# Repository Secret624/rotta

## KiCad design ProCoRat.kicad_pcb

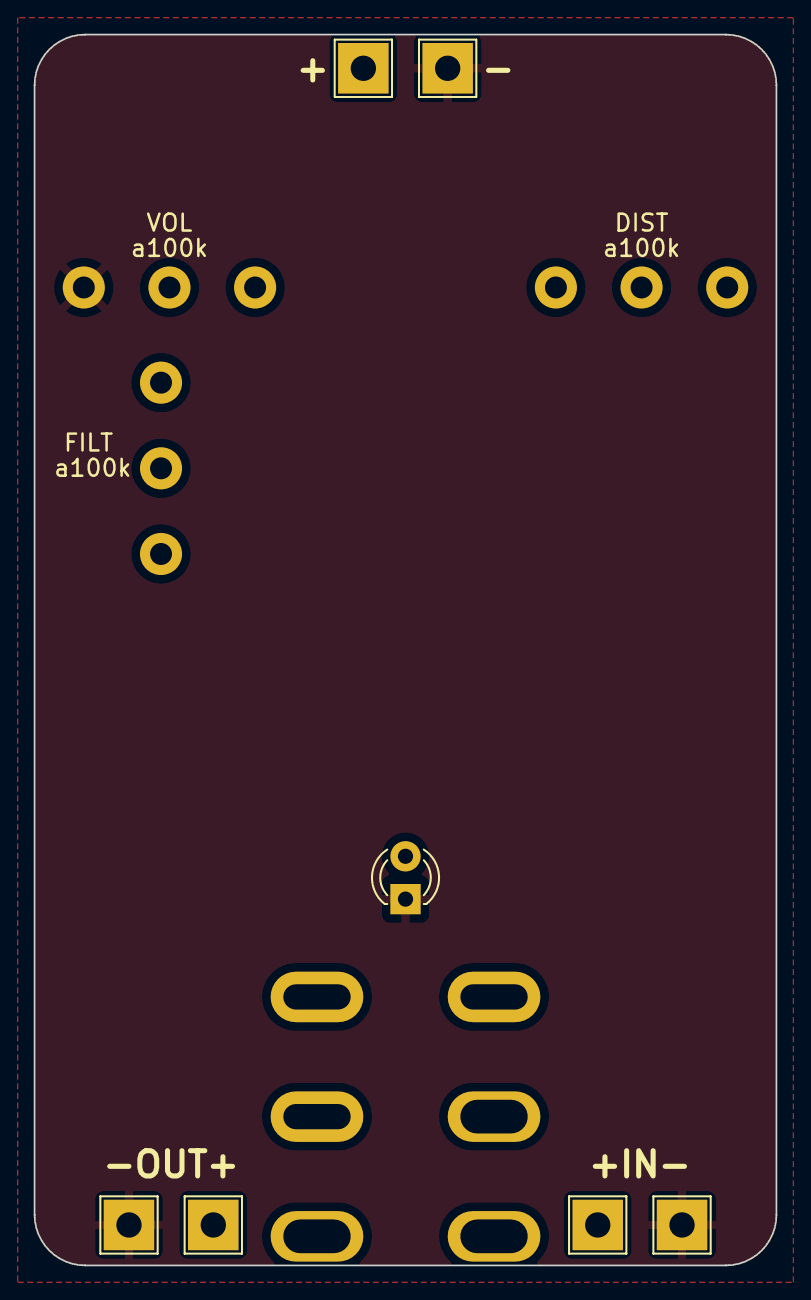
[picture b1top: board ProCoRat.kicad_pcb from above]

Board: 2 copper layers, 44.0 x 73.0 mm, 12 parts (0 on the bottom side), 6 nets, no tracks yet.

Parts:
E1: 1590B; 1590B predrilled
LED1: LED_Small; LED_D3.0mm
RV1, RV2, RV3: a100k; UT right angle long pin
SW1: SW_DPDT_x2; Ural dpdt
TP1: 9V; TestPoint_THTPad_3.0x3.0mm_Drill1.5mm
TP2: IN; TestPoint_THTPad_3.0x3.0mm_Drill1.5mm
TP3: OUT; TestPoint_THTPad_3.0x3.0mm_Drill1.5mm
TP4, TP5, TP6: GND; TestPoint_THTPad_3.0x3.0mm_Drill1.5mm

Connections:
/IN: SW1.2 (B), TP2.1
/OUT: SW1.3 (C), SW1.6 (C), TP3.1
/OUT_pcb: RV1.2, SW1.5 (B)
GND: LED1.1 (K), RV1.1, TP4.1, TP5.1, TP6.1
unnamed: RV3.2, RV3.3
unnamed: RV2.2, RV2.3
